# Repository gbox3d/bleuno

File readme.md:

# BLEuno (ble led controller)

## 프로젝트 구성

- 이 저장소는 BLEuno 펌웨어와 [하드웨어](hardware/README.md)를 관리합니다.
- [BLEuno type_m / v1](hardware/type_m/v1/README.md)은 지정 EasyEDA 마더보드를 KiCad로 이전한 하드웨어입니다. 모델명은 `type_m`, 하드웨어 리비전은 `v1`이며, 프로젝트명은 `type_m_v1`입니다. 펌웨어 버전 `1.0.5_dev`와 별도로 관리합니다.
- [BLEuno type_m / v1.1](hardware/type_m/v1.1/README.md)은 원본 v1을 보존하고 SEN1–GPIO20 배선을 추가한 뒤, 2026-11-01 전원부 수정으로 배터리 커넥터 극성 표시·이름(`BAT`)과 전원 스위치 J2의 직렬 연결(배터리 + → VIN → J2 → VCC)을 바로잡은 수정본입니다. [KiCad 프로젝트](hardware/type_m/v1.1/kicad/type_m_v1_1.kicad_pro)의 DRC 오류·미배선·회로도/PCB 차이는 0, ERC는 오류 20·경고 26이며, 제작·실물 검증은 완료하지 않았습니다. 수정 전후 그림은 [전원부 수정 확인 화면](hardware/type_m/v1.1/validation/power-fix-2026-11-01/review.html)에 있습니다.
- [BLEuno type_s / v1](hardware/type_s/v1/README.md)은 `ZeroFactorySensorBoard / Board_DHT` 원본의 센서·입출력 커넥터 보드입니다. [원본 핀맵](hardware/type_s/v1/pinmap.md)에 연결과 저항값 확인 사항을 기록했습니다. 센서 실장·펌웨어 지원·실물 동작 검증을 뜻하지 않습니다.
- **두 보드의 수업 배치는 보류하고 type_m 보드 완성을 우선합니다.** 센서는 DHT11·DHT22를 선택했고 GPIO20 지원을 추가합니다. [교재의 SmartIO 및 bleuno 공통 코드](https://github.com/gbox3d/teaching_repo/tree/main/android_programming/bleuno)는 기존 자료로 유지합니다.
- 현재 type_s 전용 펌웨어는 없으며, 기존 LED 4핀 설정 `ledpin=[4,3,1,0]`은 type_s의 센서·배터리 분압 입력과 충돌합니다. 기존 수업 설정을 두 보드에 바로 적용하지 않습니다.
- type_m 펌웨어와 독립 앱 `TypeMControl`의 구현·BLE 실기 검증 범위는 아래 기록을 따릅니다. 센서 배선 연속성·실제 온습도 측정과 모터·서보 부하 검증은 남아 있습니다.
- [bleunoApp/BleunoTest](https://github.com/gbox3d/bleunoApp/tree/main/BleunoTest)는 보드 점검·강의자 시연용 독립 앱입니다.
- AI 작업 인수인계: [_forAI/README.md](_forAI/README.md).

## type_m 모터·서보·DHT 제어

type_m v1은 **`type_m` 빌드 환경 / `type_m/1` 프로토콜**을 사용합니다. 모터 2개·서보 2개의 `1.0.0` 검증 기록을 보존하며, **`1.1.0`에 DHT11·DHT22 지원을 추가하고 보드에 업로드했습니다.** 독립 앱 `bleunoApp/TypeMControl`의 DHT 화면도 구현했고 단위 테스트 34개·Lint 문제 없음, IM_L101(API34) 설치·연결·종류 선택·오류 표시·정지·배경 전환을 확인했습니다. [빌드·핀맵·명령·정지 동작 가이드](docs/type_m.md)와 [기존 90분 실습 참고 자료](https://github.com/gbox3d/teaching_repo/blob/main/android_programming/bleuno/type_m_lab.md)가 있으며, 수업 적용은 보드 완성 뒤 결정합니다.

센서 포트 **J7은 패드 1=3.3V, 2=SEN1, 3=GND**입니다. 원본 v1은 SEN1–MCU 연결이 누락돼 있습니다. **v1.1 수정본은 J7.2·R3.2·U1 패드15(GPIO20)를 SEN1으로 연결**하고 R3 10kΩ 풀업을 유지합니다. 원본 v1은 보존하며, 설계 파일 수정만으로 이미 실장한 v1의 물리 배선이 바뀌지는 않습니다. J7.2–U1 패드15 점퍼는 기존 v1의 임시 보수 방법일 뿐 정규 사용 절차가 아니며, 현재 작업은 v1.1 설계 수정입니다. 사용자는 DHT22를 SENSOR1에 연결했다고 확인했고 실제 온습도 측정은 아직 성공하지 못했습니다. v1.1 전원부에서는 배터리 +가 스위치 J2를 거쳐 VCC로 가며(1=OFF, 2=COM, 3=ON), 스위치 접점 정격과 USB·배터리 동시 연결 주의는 [v1.1 안내](hardware/type_m/v1.1/README.md#전원-경로와-주의)를 따릅니다. [리비전별 연결·전원 조건](docs/type_m.md#dht11dht22-연결과-조회)을 확인하세요.

1.1.0의 `dht 11`/`dht 22`로 종류를 선택하고 `dht`로 조회합니다. 펌웨어 기본은 DHT11이고 앱은 선택한 종류를 저장하며, 측정 주기는 2500ms입니다. 응답 예시 `dht 22 253 614`는 25.3°C·61.4%RH를 뜻하며 준비 중에는 `wait`, 읽기 실패에는 `error`를 반환합니다. 센서 읽기 실패 자체는 BLE 연결·모터 READY를 해제하지 않습니다. **1.1.0 호스트 501 checks·빌드·COM11 업로드/hash 검증·BLE 비구동 54 checks를 통과했습니다.** 실제 시험에서는 두 종류 모두 `error`였고, 종류 변경 직후 `wait`와 실패 후 READY 유지·STOP·watchdog·재연결을 확인했습니다. 앱에서도 DHT22 선택 유지, STOP·Home 단절 후 내부 출력 0을 확인했습니다. 실제 온습도 수치는 아직 검증하지 않았습니다.

저장소 루트에서 이미 설치된 Python을 `uv`로 재사용합니다. Python을 새로 설치하거나 자동 다운로드하지 않습니다.

```powershell
uv python list --only-installed
uv run --no-python-downloads --python 3.12 --with platformio==6.2.0 python -m platformio run -e type_m
# COMxx는 현재 확인한 보드 포트로 바꿉니다.
uv run --no-python-downloads --python 3.12 --with platformio==6.2.0 python -m platformio run -e type_m --target upload --upload-port COMxx
```

CCCD 알림 구독 → `about`의 모델·버전 확인 → `ready`/`ok ready`를 마쳐야 제어할 수 있습니다. 1.0.0의 응답은 `type_m/1 fw=1.0.0`, DHT 확장 버전은 `type_m/1 fw=1.1.0`입니다. 상태 RGB는 대기 빨강 점멸 → BLE 연결 파랑 점멸 → 준비 완료 파랑 고정입니다. `stop`은 양 모터와 양 서보 펄스를 끄며, 1500ms watchdog과 앱의 500ms heartbeat를 함께 사용합니다.

사용자는 type_m v1을 설계대로 실장했으며, 모듈은 RGB가 있는 EstarDyn ESP32-C3 SuperMini Plus V2.0이라고 확인했습니다. GPIO8 NeoPixel 설정으로 업로드 뒤 대기 빨강 점멸과 준비 완료 파랑 고정을 확인했습니다. 준비 전 파랑 점멸은 소스·상태 기준입니다. GPIO0은 배터리 ADC이므로 LED 시험 출력으로 쓰지 않습니다. 아래 기존 LED/DHT 명령과 `Config` 설정은 type_m에 적용하지 않습니다.

**1.0.0 기준으로** 호스트 **399 checks**, Android 단위 **17개**·Lint, 펌웨어 빌드·업로드, BLE 비구동 검사 **29개**를 통과했습니다. IM_L101(API34)에서 보드 검색·CCCD/about/ready·STOP 응답·배경 진입 후 연결 해제·재연결 준비를 확인했고 내부 출력 상태는 모두 0이었습니다. 업로드한 COM11/MAC 끝자리 `b3:6e`와 최초 COM14/`54:d5`의 4MB 백업은 각각 보존했습니다. 이 결과를 1.1.0 DHT 검증으로 확대하지 않습니다. 0이 아닌 모터 명령·유효한 서보 명령과 실제 파형·부하 시험은 수행하지 않았습니다. [검증 현황과 백업 해시](docs/type_m.md#대상과-현재-확인-범위)를 확인하세요.

## Description
This is a simple BLE LED controller that can be used to control an LED over BLE. The controller is implemented using the ESP32 microcontroller and the Arduino framework. The controller can be used to turn the LED on and off, as well as to change the color of the LED.

devoce name start with `ESP32_BLE'  

## uuid

The UUIDs for the service and characteristic are defined in the `ble_led_controller.ino` file. The UUIDs are as follows:
```cpp
#define SERVICE_UUID "c6f8b088-2af8-4388-8364-ca2a907bdeb8"
#define CHARACTERISTIC_UUID "f6aa83ca-de53-46b4-bdea-28a7cb57942e"
```

```txt
service-uuid : c6f8b088-2af8-4388-8364-ca2a907bdeb8
characteristic-uuid : f6aa83ca-de53-46b4-bdea-28a7cb57942e
```

## Commands

아래 핀 설정은 기존 보드별 사용 예시입니다. `type_m`·`type_s` v1의 확정 설정이 아니므로 [모델별 핀맵](hardware/README.md)을 먼저 확인합니다.

**setup led pins** : Setup the pins for the LED  

```txt
config setA ledpin [4,3,1,0] // espc3 tenstar  -> gpio4,gpio3,gpio1,gpio0
config setA ledpin [3,4,5,7] // espc3 -> d1,d2,d3,d5 
config setA ledpin [3,4,5,6,7,8,9] // espc3 -> d1,d2,d3,d4,d5 ,d8,d9 , (d4,d9) 는 부팅시 사용하므로 사용에 주의
config setA ledpin [1,4,6,5] 
config setA ledpin [4,16,17,18] 
config setA ledpin [2,12,15,4,13,14,16,17,18] 
config setA ledpin [0,2,5,12,15,13,14,18,19] 
config setA ledpin [15,2,0,4,16,17,18,19] //worover kit
config setA ledpin [15,2,0,4] //worover kit
config save
reboot
```

**setup pwm pins** : Setup the pins for the PWM  
```txt
config setA pwmpin [16,17,18,19] //
```

**on** : Turn the LED on   
example:    
`on 1` : turn led index 1 on  
`on 3 6 9` : turn led index 3, 6, 9 on  
`on -1` : all leds on  

**off** : Turn the LED off  
example:  
`off 1` : turn led index 1 off  
`off 3 6 9` : turn led index 3, 6, 9 off 
`off -1` : all leds off  

**pwm** : Set the PWM value for the LED
example:
`pwm -1 255` : set all pwm value to 255
`pwm 0 255` : set the PWM value for led index 1 to 255

dht11 pin setup
```txt

config set dht11pin 7

config set dht11pin 32
config save
reboot
```
**safe back delay** : Set the safe back mode for the LED
example:  
```txt
config set safebackdelay 0
config set safebackdelay 500
config save
```

## board info

### esp32c3 tenstar

**주의 사항**

- 사용해도 되는 핀 : 0, 1, 3, 4, 5, 6, 7, 10   
- 아날로그 입력 핀 (ADC) : 0, 1, 2, 3, 4, 5 (보드에 A0~A5로 표기됨)  
- PWM 핀 : 모든핀 가능  
- i2c 는 가능한 4,5번 핀을 사용하세요.    
- 8 번핀 : 내장 ws2812 용도 neo 픽셀 사용시 8번 핀을 사용합니다.  
- 2,9 번핀 : 부팅시 사용하므로 사용에 주의하세요.   
- 5 번핀은 wifi 사용시 값이 불안정할 수 있습니다.  

```txt
config setA ledpin [4,3,1,0] // espc3 tenstar  -> gpio4,gpio3,gpio1,gpio0
config set dht11pin 7
config save

reboot
```

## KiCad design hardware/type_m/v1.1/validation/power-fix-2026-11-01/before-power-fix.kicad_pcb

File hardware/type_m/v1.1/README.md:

# BLEuno type_m v1.1

[원본 v1](../v1/README.md)을 그대로 보관하고 별도로 수정한 하드웨어 리비전입니다. 2026-11-01에 두 단계로 수정했습니다.

1. **센서 배선** — 원본에서 빠져 있던 SENSOR1 신호(SEN1) → C3 GPIO20 연결을 회로도와 PCB에 추가.
2. **전원부** — 배터리 커넥터 J1의 극성 표시와 이름을 바로잡고, 전원 스위치 J2가 실제로 배터리와 부하 사이의 직렬 경로가 되도록 네트와 배선을 수정.

v1.1은 아직 제작하지 않았으므로 두 수정을 같은 리비전으로 관리합니다. **이 파일 수정으로 이미 실장된 v1 보드의 배선이 바뀌지는 않습니다.** 제작·실물 통전·배터리 구동·모터/서보 부하 검증은 아직 하지 않았습니다.

**[KiCad 프로젝트 열기](kicad/type_m_v1_1.kicad_pro)** · **[전원부 수정 확인 화면](validation/power-fix-2026-11-01/review.html)** · **[센서 연결 확인 화면](validation/preview/review.html)** · [회로도 PDF](validation/preview/type_m_v1_1-schematic.pdf)

## 센서 배선 수정 (1단계)

- SEN1의 연결: **J7.2(SENSOR1 가운데 신호 핀) ↔ R3.2(기존 10 kΩ 풀업) ↔ U1.15(GPIO20)**.
- U1의 `15`는 모듈 심볼/풋프린트의 패드 번호입니다. 실제 C3 보드에 표시된 GPIO 번호는 **20**입니다.
- MCU 심볼의 잘못된 핀 이름을 바로잡았습니다: 패드 15 `GPIO21 → GPIO20`, 패드 16 `GPIO22 → GPIO21`. 패드 16은 연결하지 않습니다.
- 새 배선 6개(폭 0.254 mm)와 비아 1개(외경 0.6 mm / 드릴 0.3 mm)를 추가했습니다. PCB 실크에 `type_m v1.1`을 표시했습니다.
- SENSOR1의 기존 3.3 V 전원, GND, 10 kΩ 풀업과 부품 위치·외곽·기존 배선을 유지했습니다. DHT11/DHT22를 사용하며 앱에서 센서 종류를 선택합니다.

GPIO20은 UART0 RX와 일반 GPIO를 겸합니다. 현재 type_m 펌웨어의 USB HWCDC는 GPIO18/19를 사용하므로 GPIO20을 DHT 입력으로 사용할 수 있습니다. GPIO20에 외부 UART RX를 동시에 연결하는 구성은 지원하지 않습니다. [Espressif GPIO 문서](https://docs.espressif.com/projects/esp-idf/en/stable/esp32c3/api-reference/peripherals/gpio.html)

## 전원부 수정 (2단계)

[수정 전 검토](validation/power-audit-2026-11-01/design-review.md)에서 확인한 3건을 고쳤습니다. 수정 전후 그림과 수치는 [전원부 수정 확인 화면](validation/power-fix-2026-11-01/review.html)에 있습니다.

| 항목 | 수정 전 | 수정 후 |
|---|---|---|
| J1 극성 표시 | 실크 `BAT + -` 한 줄. 전면 기준 왼쪽 원형 패드 J1.2 = GND(−), 오른쪽 사각 패드 J1.1 = 배터리 + 이므로 좌우 순서가 반대 | 실크 `BAT`(원래 자리) + 각 패드 바로 위에 `−`(J1.2) / `+`(J1.1) 0.8 mm 표시. 패드 네트는 바꾸지 않음 |
| 전원 스위치 J2 | J1.1과 J2.2가 모두 VCC, J2.3의 `VIN`은 고립 패드 → J2로 전원을 끊을 수 없음 | J1.1(배터리 +) → **VIN** → J2.3. J2.2(공통) → **VCC** → 부하. J2.1은 OFF 위치로 의도적 미연결(회로도 NC 표시) |
| J1 이름 | 회로도·PCB 값 `MT1`(모터 출력 J3와 같은 이름) | `BAT` |

PCB 변경은 J1.1에서 내려오던 1.0 mm 배선 3개의 네트를 VIN으로 바꾸고, VCC 노드로 이어지던 대각 배선 1개를 삭제한 뒤, (172.385, 96.731)에서 J2.3 패드 중심 (172.385, 93.048)까지 1.0 mm F.Cu 배선 1개를 추가한 것입니다. 가장 가까운 다른 네트 패드(J2.2)와의 간격은 1.19 mm이고, 주변 GND 채움 동판과는 설계 규칙 간격 0.254 mm를 둡니다. 센서 배선·비아, 외곽, 나머지 부품과 배선은 바꾸지 않았고 동판은 KiCad에서 다시 채웠습니다. 새 `−`/`+` 표시의 글자 획은 패드 구리에서 각각 0.64 mm·0.33 mm, 보드 외곽선 중심에서 0.65 mm·0.47 mm(외곽 선폭 안쪽 기준 0.34 mm) 떨어져 있습니다. 이 프로젝트 규칙에는 실크–외곽 최소 간격이 없어 DRC가 검사하지 않는 값이며, 일반적인 제작사 최소값(0.15–0.2 mm)보다는 큽니다.

### J2 스위치 사용 규칙

| 패드 | 위치 (전면, 왼쪽부터) | 네트 | 역할 |
|---|---|---|---|
| J2.1 (사각) | 왼쪽, `OFF` 쪽 | 없음 (NC) | 슬라이드 스위치 OFF 위치 접점. 아무것도 연결하지 않음 → 배터리 분리 |
| J2.2 | 가운데 | **VCC** | 스위치 공통(COM). U1 5V 핀, DRV8833, 서보 2개, R1 분압으로 전원이 나감 |
| J2.3 | 오른쪽, `ON` 쪽 | **VIN** | 배터리 + 입력(J1.1). 스위치가 2–3을 이으면 ON |

- 실크 `PW OFF ON`은 왼쪽이 OFF, 오른쪽이 ON 방향입니다. 슬라이드 스위치 손잡이를 오른쪽(BAT 커넥터 쪽)으로 밀면 2–3이 이어져 ON입니다. 글자 `OFF`/`ON`이 패드 1/3 중심에 정확히 놓인 것은 아닙니다.
- 스위치 대신 **2–3 핀 쇼트 점퍼**를 꽂으면 항상 ON입니다.
- J2 접점에는 모터 드라이버·서보 2개·MCU의 전체 부하 전류가 흐릅니다. 2.54 mm 소형 슬라이드 스위치(SS12D00 계열)는 접점 정격이 0.3–0.5 A 수준이라 모터·서보 피크 전류에 부족할 수 있습니다. 부하 전류 예산을 확인하기 전에는 쇼트 점퍼로 운용하거나 피크 전류 이상 정격의 스위치를 선택합니다. 보드 배선 폭은 1.0 mm입니다.

### 전원 경로와 주의

- 배터리 + → J1.1 → VIN → (J2 ON) → VCC → U1.8(모듈 `5V` 핀), U2.9(DRV8833 VCC), J5.1/J6.1(서보 +), R1.1(CHKBAT 분압). 배터리 − → J1.2 → GND.
- CHKBAT(R1 220 kΩ / R2 220 kΩ)는 VCC 쪽에 그대로 두었습니다. 스위치 ON이면 GPIO0이 배터리 전압의 1/2을 읽고, OFF이면 분압 전류(약 9 µA)도 흐르지 않으며 꺼진 MCU의 GPIO0에 전압이 걸리지도 않습니다. 분압을 VIN 쪽으로 옮기면 OFF 상태에서 110 kΩ(R1∥R2)을 통해 VIN/2이 꺼진 핀에 걸리므로 옮기지 않았습니다.
- U1의 `5V` 핀은 VCC에 그대로 있습니다. 보관 중인 판매자 매뉴얼(`.local/type_m/estardyn-manual.pdf` 6장)은 5V 핀 입력을 **정전압 5 V ±0.2 V**로 적고 **Type-C와 5V 핀 동시 급전을 금지**합니다. 모듈 내부 회로는 KiCad에 없으므로 실물 동작을 단정하지 않지만, 아래는 설계상 사실입니다.
  - 스위치 OFF는 **배터리만** 분리합니다. USB가 꽂혀 있고 모듈이 USB 전원을 5V 핀으로 내보내는 구조라면 모터 드라이버·서보는 USB에서 계속 전원을 받습니다.
  - 모듈이 USB 5 V를 5V 핀으로 내보내는 구조라면, 스위치 ON 상태로 USB를 꽂을 때 USB 5 V와 배터리가 VCC에서 만납니다. 이 보드에는 충전·보호 회로가 없으므로, 모듈의 USB→5V 핀 경로를 확인하기 전에는 리튬 배터리를 연결한 채 ON + USB로 두지 않습니다. 이 상태의 CHKBAT는 배터리가 아니라 USB가 공급하는 VCC를 읽습니다.
  - 원본 v1은 배터리가 항상 VCC에 직결되어 있어 이 상태를 피할 수 없었습니다.
- 3.7 V 배터리 직결 적합성, 승압 필요 여부, 사용자 보고(USB 부팅 O / 배터리 부팅 X, 4.9 V 측정)의 원인은 이 수정에서 판단하지 않았습니다.

## 확인 방법

1. [회로도](kicad/type_m_v1_1.kicad_sch): J1 아래 값 `BAT`, J1.1의 `VIN` 라벨과 J2.3의 `VIN` 라벨, J2.1의 NC(×) 표시, J2.2의 VCC. U1 `GPIO20` 옆 `SEN1` 라벨과 J7 가운데 핀의 같은 라벨.
2. [PCB](kicad/type_m_v1_1.kicad_pcb): J1 패드 위 `−`/`+`. J2.3 패드에서 아래로 내려오는 VIN 배선이 J1.1에서 온 배선과 (172.385, 96.731)에서 만납니다. J2.2 패드의 기존 VCC 배선은 U1·R1·서보·드라이버로 이어집니다. SENSOR1 가운데 패드의 네트를 강조하면 U1의 GPIO20까지 연결됩니다.
3. [전원부 수정 확인 화면](validation/power-fix-2026-11-01/review.html)과 [센서 연결 확인 화면](validation/preview/review.html)의 그림을 실제 KiCad 화면과 비교합니다. 두 화면 모두 KiCad가 내보낸 SVG를 바탕으로 합니다.

## 검사 결과 (전원부 수정 후, 현재 파일 기준)

| 검사 | 결과 |
|---|---|
| KiCad 10.0.6 PCB DRC / 동판 재채움 / 회로도 일치 검사 | 오류 0, 기존 실크 글자 높이 경고 12, 미배선 0, 불일치 0 |
| 회로도 ERC | 오류 20, 경고 26. 센서 단계 21/27에서 J2.1 미연결 오류, VIN 고립 라벨 경고, J1.1–전원 심볼 핀 유형 경고가 사라지고 J1.1–J2.3 핀 유형 경고 1개가 추가됨 |
| 전원부 변경 독립 대조 ([verify_power_fix.py](validation/power-fix-2026-11-01/verify_power_fix.py)) | 34/34 PASS: 허용한 변경 외 차이 없음, 구리 접촉 그래프에서 J1.1은 J2.3에만 닿음, 서로 다른 네트의 구리 접촉 0, SEN1 배선·비아 유지, 기록 파일이 설계 파일보다 최신 |
| 원본 v1 보존 | 기록한 57개 파일의 SHA-256 불변 |

검사 자료(현재 상태): [DRC](validation/drc.json), [ERC](validation/erc.json), [netlist](validation/netlist.xml), [전원부 검증 결과](validation/power-fix-2026-11-01/power-fix-verification.json), [PCB 패치 기록](validation/power-fix-2026-11-01/pcb-power-patch.json), [회로도 패치 기록](validation/power-fix-2026-11-01/schematic-patch.json).

센서 단계(전원부 수정 전) 기록: [독립 변경 대조 25/25](validation/revision-comparison.json)와 그 입력이었던 회로도·PCB·netlist·ERC·DRC는 `validation/power-fix-2026-11-01/before-power-fix.*`로 보존했고 해시가 일치합니다. [verify_revision.py](validation/verify_revision.py)는 그 스냅샷을 기준으로 쓴 검사라 현재 파일에는 그대로 통과하지 않습니다. 현재 파일의 검사는 `verify_power_fix.py`입니다.

남은 ERC 오류 20은 no_connect 표시가 없는 미연결 핀 5(U1 GPIO2/8/9/21, U2 ULT), 전원 심볼 미구동 2(VCC, GND), 가져온 심볼의 Input 핀 유형에 따른 pin_not_driven 13이고, 경고 26은 모두 Unspecified 핀 유형 조합(pin_to_pin)입니다. 검사 통과를 위해 핀 유형이나 규칙을 완화하지 않았습니다. 제작 적합성 검토와 실물 검증은 별개입니다.

## 재검증

설치된 KiCad의 CLI와 Python을 사용합니다. Python을 새로 설치하지 않습니다.

```powershell
$kicad = "$env:LOCALAPPDATA\Programs\KiCad\10.0\bin"
& "$kicad\kicad-cli.exe" sch erc --format json --severity-all -o hardware/type_m/v1.1/validation/erc.json hardware/type_m/v1.1/kicad/type_m_v1_1.kicad_sch
& "$kicad\kicad-cli.exe" sch export netlist --format kicadxml -o hardware/type_m/v1.1/validation/netlist.xml hardware/type_m/v1.1/kicad/type_m_v1_1.kicad_sch
& "$kicad\kicad-cli.exe" pcb drc --format json --severity-all --schematic-parity -o hardware/type_m/v1.1/validation/drc.json hardware/type_m/v1.1/kicad/type_m_v1_1.kicad_pcb
& "$kicad\python.exe" -B hardware/type_m/v1.1/validation/power-fix-2026-11-01/verify_power_fix.py
```

위 명령은 `validation/`의 기록 파일을 현재 파일 기준으로 다시 씁니다. 기록을 덮어쓰지 않고 감사만 하려면 `kicad-cli`의 `-o`와 `verify_power_fix.py --output`(필요하면 `--erc/--drc/--netlist`)을 임시 폴더로 지정합니다.

`patch_schematic_sensor.py`, `patch_pcb_sensor.py`, `patch_schematic_power.py`, `patch_pcb_power.py`는 이미 적용된 수정 스크립트이며 다시 실행하지 않습니다. 전원부 스크립트 2개는 기준 해시가 다르거나 KiCad GUI가 프로젝트를 열고 있으면(`~*.lck`) 스스로 거부하고, 센서 스크립트 2개는 대상 상태로만 재적용을 거부합니다. `type_m_v1_1.kicad_prl`은 GUI 화면 설정 파일이라 기록·검증 대상이 아닙니다(`.gitignore`). KiCad GUI로 저장하기 전에는 외부에서 바꾼 파일을 다시 열어 최신 상태를 불러옵니다.

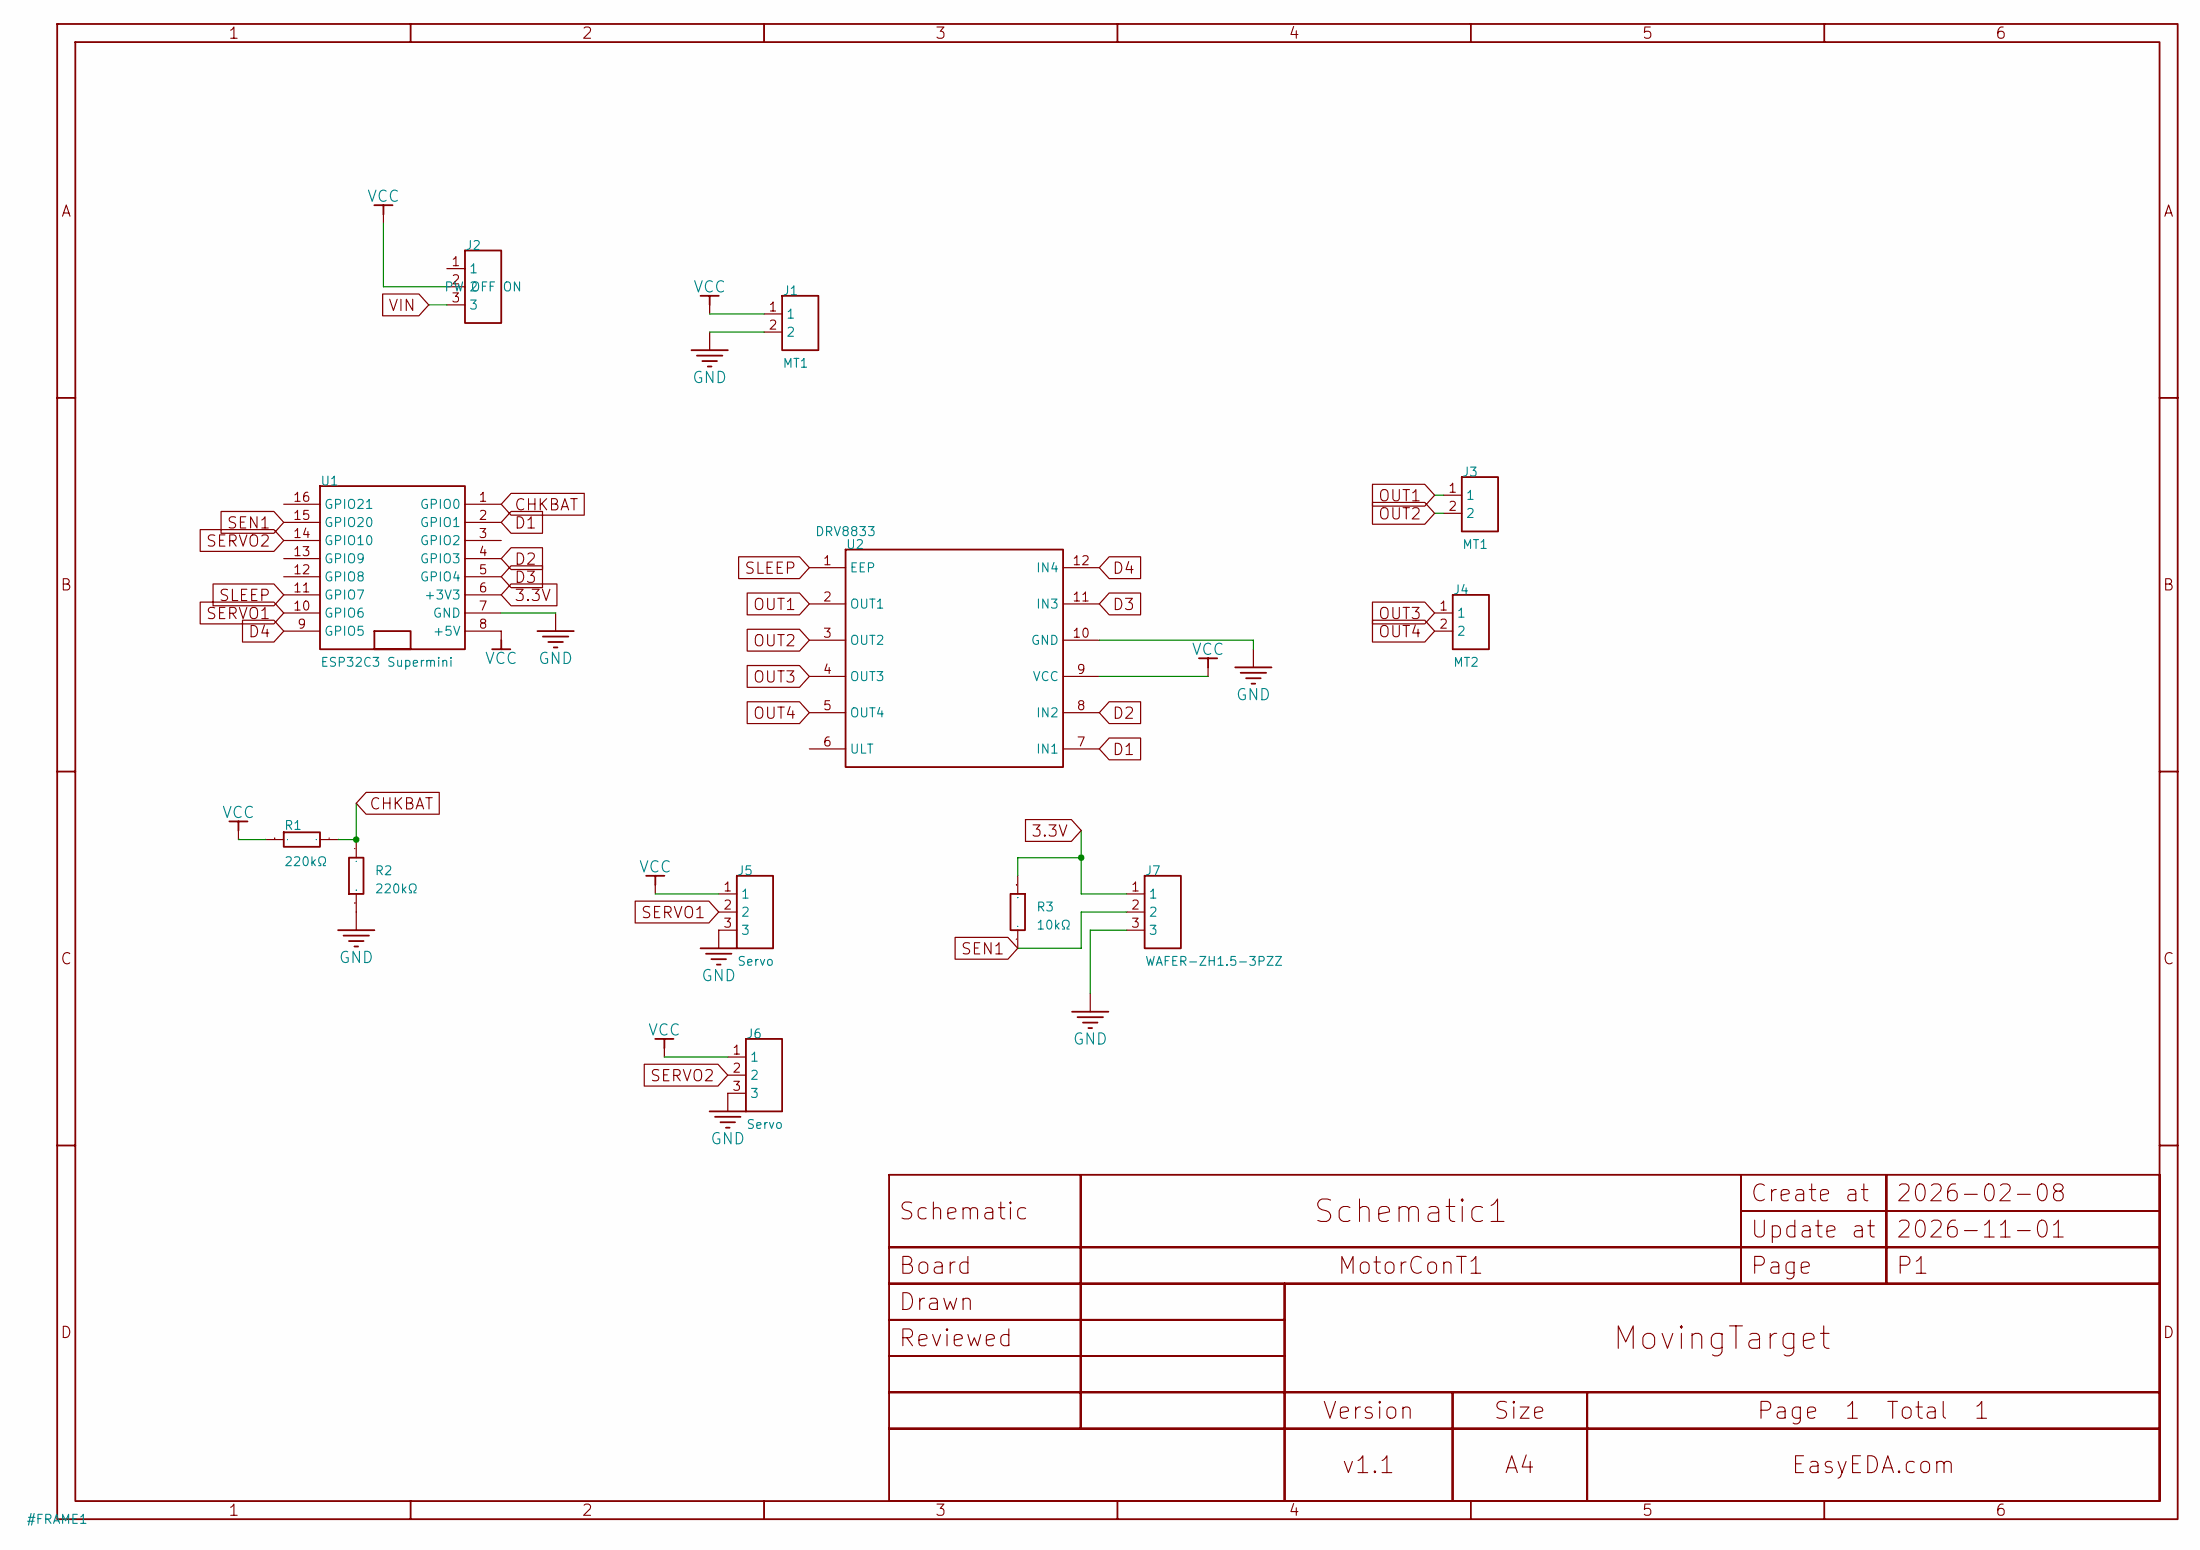
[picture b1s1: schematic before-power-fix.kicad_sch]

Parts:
J1, J3: MT1; CONN-TH_2P-P1.50_HCTL_HC-ZH1.5-2AW; Manufacturer Part BX-ZH1.5-2PWZ; LCSC Part Name 1x2P 间距:1.5mm 弯插 系列:ZH
J2: PW OFF ON; HDR-TH_3P-P2.54-V-M
J4: MT2; CONN-TH_2P-P1.50_HCTL_HC-ZH1.5-2AW; Manufacturer Part BX-ZH1.5-2PWZ; LCSC Part Name 1x2P 间距:1.5mm 弯插 系列:ZH
J5, J6: Servo; HDR-TH_3P-P2.54-V-M
J7: WAFER-ZH1.5-3PZZ; CONN-TH_3P-P1.50_A1500WV-03P; Manufacturer Part WAFER-ZH1.5-3PZZ; LCSC Part Name 1x3P 间距:1.5mm 直插 系列:ZH
R1, R2: 220kΩ; R_AXIAL-0.4
R3: 10kΩ; R_AXIAL-0.4
U1: ESP32C3 Supermini; ESP32C3 SM
U2: DRV8833

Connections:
3.3V: J7.1, R3.1, U1.6 (+3V3)
CHKBAT: R1.2, R2.2, U1.1 (GPIO0)
D1: U1.2 (GPIO1), U2.7 (IN1)
D2: U1.4 (GPIO3), U2.8 (IN2)
D3: U1.5 (GPIO4), U2.11 (IN3)
D4: U1.9 (GPIO5), U2.12 (IN4)
GND: J1.2, J5.3, J6.3, J7.3, R2.1, U1.7 (GND), U2.10 (GND)
OUT1: J3.1, U2.2 (OUT1)
OUT2: J3.2, U2.3 (OUT2)
OUT3: J4.1, U2.4 (OUT3)
OUT4: J4.2, U2.5 (OUT4)
SEN1: J7.2, R3.2, U1.15 (GPIO20)
SERVO1: J5.2, U1.10 (GPIO6)
SERVO2: J6.2, U1.14 (GPIO10)
SLEEP: U1.11 (GPIO7), U2.1 (EEP)
VCC: J1.1, J2.2, J5.1, J6.1, R1.1, U1.8 (+5V), U2.9 (VCC)
VIN: J2.3

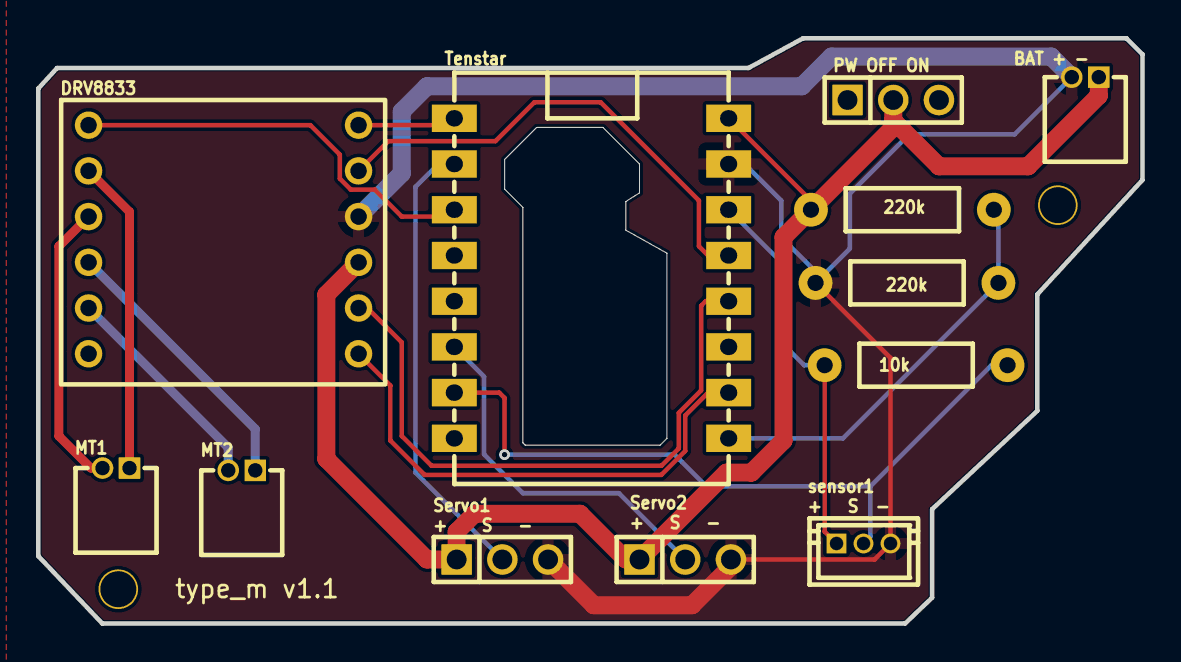
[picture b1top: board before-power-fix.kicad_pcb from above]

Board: 2 copper layers, 61.3 x 32.5 mm, 14 parts (0 on the bottom side), 16 nets.

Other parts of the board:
MP1: Pad_e1
MP2: Pad_e2

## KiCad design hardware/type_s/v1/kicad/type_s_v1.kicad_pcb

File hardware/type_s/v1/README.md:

# BLEuno type_s v1

모델은 `type_s`, 하드웨어 버전은 `v1`입니다. 지정된 EasyEDA **ZeroFactorySensorBoard → Board_DHT → PCB1**을 KiCad `type_s_v1` 프로젝트로 관리합니다. 펌웨어 버전과 하드웨어 버전은 별개입니다.

2026-11-01에 KiCad 이전과 원본 대조를 완료했습니다. 편집할 파일은 [kicad/type_s_v1.kicad_pro](kicad/type_s_v1.kicad_pro)입니다. 원본의 부품·배선·연결을 보존했으며, 아래 검증 기록에 이전 과정의 보정과 남은 항목을 기록합니다.

## 구성

| 경로 | 내용 |
|---|---|
| [source/README.md](source/README.md) | EasyEDA 원본 `.epro2`, 가져오기용 `.epro`, 출처·시간·SHA-256 |
| [kicad/type_s_v1.kicad_pro](kicad/type_s_v1.kicad_pro) | KiCad 프로젝트 |
| [kicad/type_s_v1.kicad_sch](kicad/type_s_v1.kicad_sch) | 회로도 |
| [kicad/type_s_v1.kicad_pcb](kicad/type_s_v1.kicad_pcb) | PCB |
| `kicad/type_s_v1.kicad_sym`, `kicad/type_s_v1.pretty/` | 프로젝트 전용 심볼·풋프린트 라이브러리 |
| [pinmap.md](pinmap.md) | MCU·커넥터·저항·전원 핀맵 및 원본 검토 항목 |
| [validation/README.md](validation/README.md) | 원본 대조, ERC·DRC, 보정 내역과 재검증 명령 |

## 보드 용도와 원본 차이

이 보드는 ESP32-C3 모듈과 센서·디지털·아날로그 연결용 헤더를 사용하는 마더보드입니다. `DHT`, `CDS`, `DS18B20`은 원본 커넥터의 표기이며 해당 센서가 보드에 실장되었다는 뜻은 아닙니다.

- 센서 신호: `SENSOR1` GPIO3, `SENSOR2` GPIO4, `SENSOR3` GPIO5.
- 확장 신호: `A1` GPIO1, `D1` GPIO6, `D2` GPIO7, `D3` GPIO10.
- 배터리 측정: `BATCHK` GPIO0.
- **배터리 분압 저항 R1/R2:** 원본 회로도는 각각 `220kΩ`, PCB의 상속값·표기는 각각 `10kΩ`입니다. 이전 과정에서 임의로 동일하게 만들지 않습니다. 실제 부품값을 확인한 뒤 설계 변경으로 확정해야 합니다.

기존 교재의 `ledpin=[4,3,1,0]`, `dht11pin=7` 설정은 이 보드의 센서·분압·확장 신호 배치와 다릅니다. [핀맵](pinmap.md)의 전원·커넥터 순서를 먼저 확인하고 실습에 맞는 설정을 사용합니다. 센서 실물, 전압, 모듈 핀 표기, USB/외부 전원의 관계는 별도 실기 검증 대상입니다.

## 이전 검증

최초 가져오기 파일과 원본을 별도로 보존했습니다. 원본에는 물리 부품 15개·부품 패드 52개·독립 홀 패드 3개·배선 114개·연결 네트 그룹 12개가 있습니다. 외곽은 15개 선분, 내부 절개는 8개 선분입니다.

[원본 비교 결과](validation/import-comparison.json)의 `checked_comparisons_pass`는 `true`입니다. 회로도와 PCB를 KiCad에서 다시 열어 표시·라이브러리 연결도 확인했습니다.

- PCB DRC: **오류 0개, 실크 관련 경고 39개**, 미배선 0개.
- 회로도/PCB 대응 검사: **R1/R2의 원본 값 차이 2개**가 남습니다. 다른 가져오기 연결·빈 값 표현의 차이는 정리했습니다.
- 회로도 ERC: **오류 10개, 경고 26개**. 원본 핀 유형·미연결·전원 표현에 대한 검토 항목입니다.

원본에서 표시되던 실크 15개를 복원했고 GND 구리면은 KiCad에서 재계산했습니다. 상세 범위와 한계는 [검증 기록](validation/README.md)을 기준으로 판단합니다. 파일 이전은 회로 기능이나 제작 적합성, BLE·센서 동작의 실물 검증을 대신하지 않습니다.

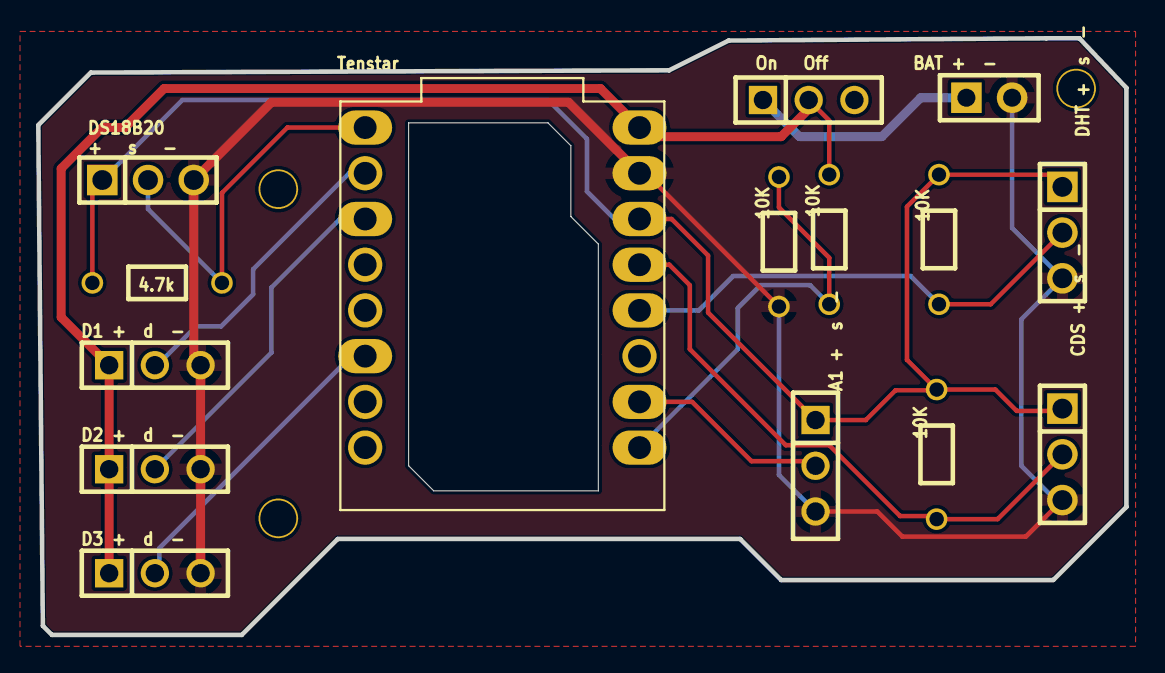
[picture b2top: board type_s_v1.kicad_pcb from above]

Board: 2 copper layers, 60.5 x 33.1 mm, 18 parts (0 on the bottom side), 12 nets.

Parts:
J1: HDR-TH_2P-P2.54-V-F
J2, J6, J7, J8, J9: HDR-TH_3P-P2.54-V-F
J3, J4, J5: HDR-TH_3P-P2.54-V-M
MP1: Pad_e1
MP2: Pad_e2
MP3: Pad_e3
R1, R2, R3, R4: 10kΩ; RES-TH_BD1.8-L3.2-P7.20-D0.4
R5: R; RES-TH_BD1.8-L3.2-P7.20-D0.4
U1: ESP32-C3; ESP32C3_SUPERMINI_CUSTOM

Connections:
3.3V: J3.1, J4.1, J5.1, J6.1, R3.1, R4.1, R5.2, U1.3.3
5V: J2.2, J7.1, J8.1, J9.1, R1.1, U1.5V
A1: J6.2, U1.1
BATCHK: R1.2, R2.1, U1.0
D1: J7.2, U1.6
D2: J8.2, U1.7
D3: J9.2, U1.10
GND: J1.2, J3.3, J4.3, J5.3, J6.3, J7.3, J8.3, J9.3, R2.2, U1.G
SENSOR1: J3.2, R3.2, U1.3
SENSOR2: J4.2, R4.2, U1.4
SENSOR3: J5.2, R5.1, U1.5
VCC: J1.1, J2.1

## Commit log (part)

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2024-12-10 off 다음에 여러개 번호예
2024-12-10 c3xiao builtin led define
2024-12-10 pwm pin 지원
2025-01-05 pwm return msg
2025-11-02 tenstar start
2025-11-22 tenstar doc
